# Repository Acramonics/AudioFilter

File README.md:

Audio Multi Filter
==================

Drawings and PCB (c) 2026 Andrew Martin, acramonics
---------------------------------------------------

This is an implementation of Jake Rothman's **Audio Multi Filter**
described in *Practical Electronics*, May 2026.

This circuit provides High-Pass, Low-Pass, Band-Pass, Notch and
All-Pass filters on a single circuit by combining combinations of
High-Pass and Low-Pass outputs.

In addition to the hardware on the board, my design requires:

- a 3P6T rotary switch,
- a DPDT (or DPST) toggle switch,
- a 10K anti-log pot,
- a dual 100K anti-log pot.

Power Supply
------------

The design includes power smoothing, but will need a dual rail power
supply providing somewhere between +/-12V and +/-18V.

Hardware
--------

### 3P6T rotary switch

The classical wafer switches are *extremely* expensive from UK
suppliers, typically #30.00 upwards per wafer! However, I have found
them at a very reasonable price (~#4.00) from AliExpress.

You could also use a 3P5T switch and replace the 1st straight through
position ('Thru') with another toggle switch.

For a stereo version, either build two boards, or if you want the same
output on both channels, you could use a 6P6T switch (if you can find
one), or a 6P5T switch (which I have seen on AliExpress at ~#5.00) and
a toggle switch to replace the Thru position.

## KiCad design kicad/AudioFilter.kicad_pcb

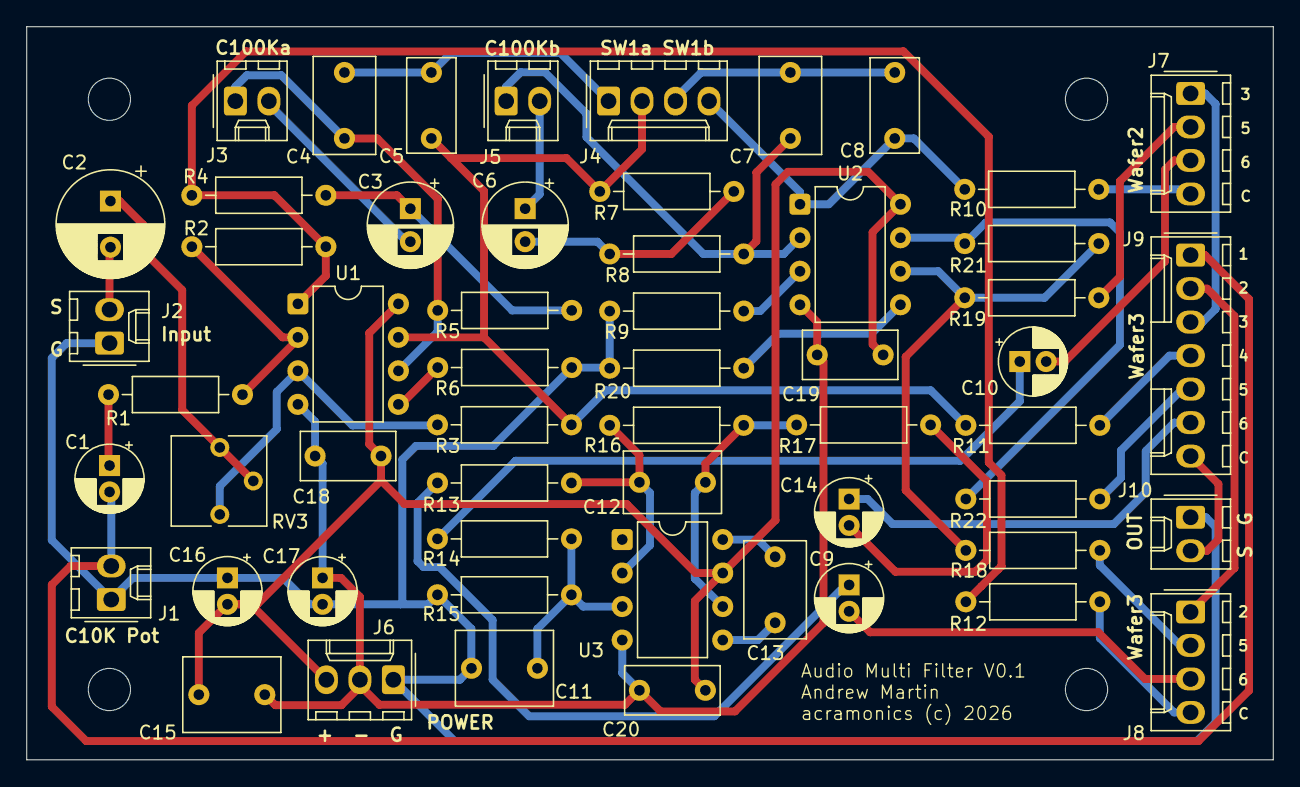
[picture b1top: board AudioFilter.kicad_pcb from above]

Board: 2 copper layers, 94.5 x 55.6 mm, 56 parts (0 on the bottom side), 45 nets.

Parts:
C1: 1uF 16V A; CP_Radial_D5.0mm_P2.00mm
C2: 220uF 25V A; CP_Radial_D8.0mm_P3.50mm
C3, C6: 100uF 25V A; CP_Radial_D6.3mm_P2.50mm
C4, C7: 100nF PP; C_Rect_L7.2mm_W4.5mm_P5.00mm_FKS2_FKP2_MKS2_MKP2
C5, C8: 6.8nF PP; C_Rect_L7.0mm_W3.5mm_P5.00mm
C9, C10: 10uF 16V; CP_Radial_D5.0mm_P2.00mm
C11: 47pF PP; C_Rect_L7.2mm_W5.5mm_P5.00mm_FKS2_FKP2_MKS2_MKP2
C12, C13: 47pF PP; C_Rect_L7.2mm_W4.5mm_P5.00mm_FKS2_FKP2_MKS2_MKP2
C14: 10uF; CP_Radial_D5.0mm_P2.00mm
C15: 470nF; C_Rect_L7.2mm_W5.5mm_P5.00mm_FKS2_FKP2_MKS2_MKP2
C16, C17: 10uF 25V; CP_Radial_D5.0mm_P2.00mm
C18, C19, C20: 100nF; C_Rect_L7.0mm_W3.5mm_P5.00mm
J1, J2, J3, J5, J10: Conn_01x02_Pin; Molex_KK-254_AE-6410-02A_1x02_P2.54mm_Vertical
J4, J7, J8: Conn_01x04_Pin; Molex_KK-254_AE-6410-04A_1x04_P2.54mm_Vertical
J6: Conn_01x03_Pin; Molex_KK-254_AE-6410-03A_1x03_P2.54mm_Vertical
J9: Conn_01x07_Pin; Molex_KK-254_AE-6410-07A_1x07_P2.54mm_Vertical
R1, R2, R18, R19, R21: 22K; R_Axial_DIN0207_L6.3mm_D2.5mm_P10.16mm_Horizontal
R3: 4K7; R_Axial_DIN0207_L6.3mm_D2.5mm_P10.16mm_Horizontal
R4, R7: 620R; R_Axial_DIN0207_L6.3mm_D2.5mm_P10.16mm_Horizontal
R5, R8: 330K; R_Axial_DIN0207_L6.3mm_D2.5mm_P10.16mm_Horizontal
R6, R9, R20, R22: 470R; R_Axial_DIN0207_L6.3mm_D2.5mm_P10.16mm_Horizontal
R10, R11, R12, R17: 100R; R_Axial_DIN0207_L6.3mm_D2.5mm_P10.16mm_Horizontal
R13, R14, R15: 10K; R_Axial_DIN0207_L6.3mm_D2.5mm_P10.16mm_Horizontal
R16: 12K; R_Axial_DIN0207_L6.3mm_D2.5mm_P10.16mm_Horizontal
RV3: 1K; Potentiometer_Vishay_T73YP_Vertical
U1, U2: NE5532; DIP-8_W7.62mm
U3: NE5534; DIP-8_W7.62mm

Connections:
+15V: C15.2, C16.2, C18.2, C19.2, C20.2, J6.3, U1.8 (V+), U2.8 (V+), U3.7 (V+)
-15V: C15.1, C17.1, C18.1, C19.1, C20.1, J6.2, U1.4 (V-), U2.4 (V-), U3.4 (V-)
/ALL.OUT: C14.1, J9.6
/BP: J9.4, R11.1
/HP.ALL: C9.2, J8.3
/HP.IN: J8.4, R12.1
/HP.NOTCH: J8.2, R18.2
/HP.OUT: J8.1, J9.2
/LP.ALL: C10.2, J7.3
/LP.IN: J7.4, R10.1
/LP.NOTCH: J7.2, R19.2
/LP.OUT: J7.1, J9.3
/NOTCH.OUT: J9.5, R22.1
/P1.2: C2.2, J2.2
/P2a.1: C3.2, J3.2
/P2a.2: C4.1, J3.1, R5.2, U1.6 (-)
/P2b.1: C6.1, J5.2
/P2b.2: C7.1, J5.1, R8.2, U2.2 (-)
/SW4.OUT: J9.7, J10.2
/THRU: C1.2, J1.2, J9.1
GND: C11.1, C16.1, C17.2, J1.1, J2.1, J6.1, J10.1, R6.1, R9.1, R15.2, R20.2
unnamed: C1.1, R1.1
unnamed: C2.1, RV3.2, RV3.3
unnamed: C3.1, R4.2, R5.1
unnamed: C6.2, R7.2, R8.1
unnamed: C9.1, R13.2
unnamed: C10.1, R14.2
unnamed: C12.2, R16.2, R17.2, U3.6
unnamed: C14.2, R17.1
unnamed: C4.2, C5.1, J4.1
unnamed: C5.2, J4.2, R3.2, R7.1, R11.2, U1.7
unnamed: C7.2, C8.1, J4.3
unnamed: C8.2, J4.4, R10.2, U2.1
unnamed: R2.2, R4.1, R12.2, U1.1
unnamed: R21.1, R22.2, U2.7
unnamed: R3.1, RV3.1, U1.3 (+)
unnamed: R1.2, R2.1, U1.2 (-)
unnamed: R6.2, U1.5 (+)
unnamed: R9.2, U2.3 (+)
unnamed: R20.1, U2.5 (+)
unnamed: R18.1, R19.1, R21.2, U2.6 (-)
unnamed: C11.2, R14.1, R15.1, U3.3 (+)
unnamed: C12.1, R13.1, R16.1, U3.2 (-)
unnamed: C13.2, U3.5 (COMP)
unnamed: C13.1, U3.8 (C/B)

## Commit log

2026-05-08 Visual layout tweaks
2026-05-08 Added README
2026-05-08 Modified README
2026-05-08 Some tidying up
2026-05-10 Component size adjustments

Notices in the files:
kicad/AudioFilter.kicad_pcb:
acramonics (c) 2026
